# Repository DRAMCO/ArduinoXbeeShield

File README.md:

# Arduino Xbee Shield by [DRAMCO](www.dramco.be)

## Required Hardware

- Xbee module
- [Digi XBee interface board](https://www.digi.com/products/models/xbib-u-dev)
- Arduino Uno
- DRAMCO XBee Shield

## Getting Started Guide

1. Install [XCTU](https://www.digi.com/products/xbee-rf-solutions/xctu-software/xctu).
2. Connect the XBee module to the [Digi interface board](https://www.digi.com/products/models/xbib-u-dev)
3. Open XCTU and connect to the interface board
4. Configure the XBee module as required. For instance, set the `AP` parameter to API enabled with PPP.
5. Connect the XBee module to the shield
6. Connectthe shield to an Arduino UNO
7. Open your favourite Arduino IDE and download an XBee library. For example [this one](https://github.com/andrewrapp/xbee-arduino).
8. Start designing cool stuff!

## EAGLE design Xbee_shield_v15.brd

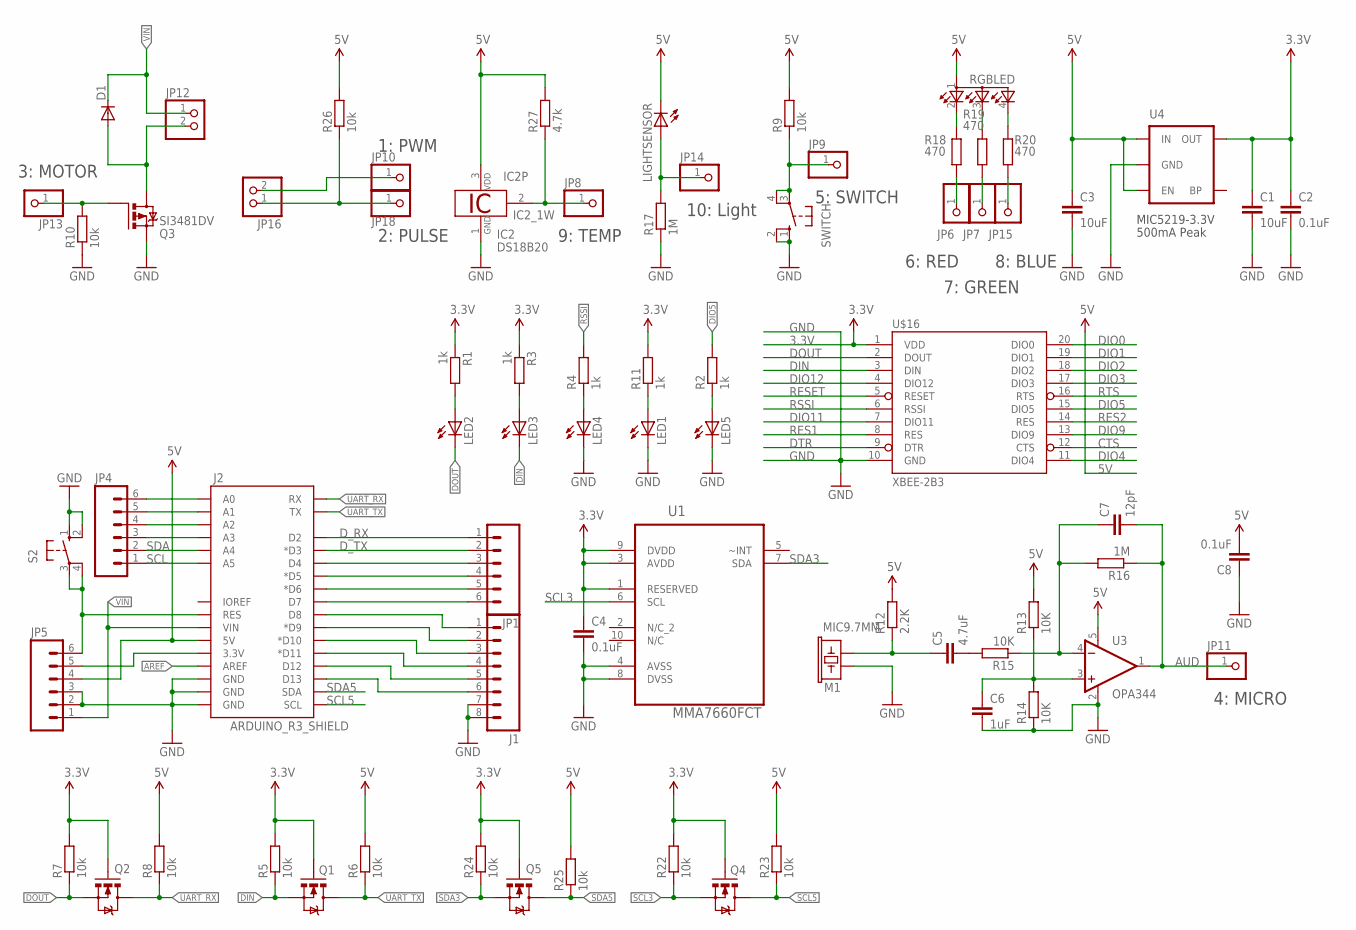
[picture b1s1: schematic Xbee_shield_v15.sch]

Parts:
C1, C3: 10uF; C0805
C2, C4, C8: 0.1uF; C0805
C5: 4.7uF; C0805
C6: 1uF; C0805
C7: 12pF; C0805
D1: DIODE-DO214AA; DO214AA
IC2: DS18B20; TO92-
J1: M08; 1X08_ROUND
J2: ARDUINO_R3_SHIELD; UNO_R3_SHIELD
JP1, JP4, JP5: M06SIP; 1X06
JP6, JP7, JP8, JP9, JP10, JP11, JP13, JP14, JP15, JP18: PINHD-1X1; 1X01
JP12, JP16: PINHD-1X2; 1X02
LED1, LED2, LED3, LED4, LED5: LEDCHIPLED_0805; CHIPLED_0805
LIGHTSENSOR: LED5MM
M1: MIC9.7MM; MIC-9.7MM
Q1, Q2, Q4, Q5: MOSFET-NCHANNELSMD; SOT23-3
Q3: SI3481DV; TSOP-6.PAC
R1, R2, R3, R4, R11: 1k; R0805
R5, R6, R7, R8, R9, R10, R22, R23, R24, R25, R26: 10k; R0805
R12: 2.2K; R0805
R13, R14, R15: 10K; R0805
R16, R17: 1M; R0805
R18, R19, R20: 470; R0805
R27: 4.7k; R0805
RGBLED: TOPLED-3; P-LCC-4-3
S2: 10-XX; B3F-10XX
SWITCH: 10-XX; B3F-10XX
U1: MMA7660FCT; DFN300X300X100-10N
U3: OPA344; SOT23-5
U4: V_REG_LDOSMD; SOT23-5
U$16: XBEE-2B3; XBEE-SMD

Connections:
3.3V: C1.1, C2.1, C4.1, Q1.1 (G), Q2.1 (G), Q4.1 (G), Q5.1 (G), R1.1, R3.1, R5.2, R7.2, R11.2, R22.2, R24.2, U1.1 (RESERVED), U1.3 (AVDD), U1.9 (DVDD), U4.5 (OUT), U$16.1 (VDD)
5V: C3.1, C8.2, IC2.3 (VDD), J2.5V, JP5.4, LIGHTSENSOR.K (C), R6.2, R8.2, R9.2, R12.2, R13.2, R23.2, R25.2, R26.2, R27.2, RGBLED.1 (A2), U3.5 (V+), U4.1 (IN), U4.3 (EN)
AREF: J2.AREF
AUD: C7.2, JP11.1, R16.1, U3.1 (OUT)
CTS: U$16.12 (CTS)
DIN: LED3.C, Q1.2 (S), R5.1, U$16.3 (DIN)
DIO0: U$16.20 (DIO0)
DIO1: U$16.19 (DIO1)
DIO2: U$16.18 (DIO2)
DIO3: U$16.17 (DIO3)
DIO4: U$16.11 (DIO4)
DIO5: R2.2, U$16.15 (DIO5)
DIO9: U$16.13 (DIO9)
DIO11: U$16.7 (DIO11)
DIO12: U$16.4 (DIO12)
DOUT: LED2.C, Q2.2 (S), R7.1, U$16.2 (DOUT)
DTR: U$16.9 (DTR)
D_RX: J2.D2, JP1.1
D_TX: J2.D3 (*D3), JP1.2
GND: C1.2, C2.2, C3.2, C4.2, C6.2, C8.1, IC2.1 (GND), J1.7, J1.8, J2.GND@0 (GND), J2.GND@1 (GND), J2.GND@2 (GND), JP5.2, JP5.3, LED1.C, LED4.C, LED5.C, M1.2, Q3.4 (S), R10.1, R14.1, R17.1, S2.1 (S), S2.2 (S1), SWITCH.1 (S), SWITCH.2 (S1), U1.4 (AVSS), U1.8 (DVSS), U3.2 (V-), U4.2 (GND), U$16.10 (GND)
unnamed: LED2.A, R1.2
unnamed: LED4.A, R4.1
unnamed: J1.6, J2.D13
unnamed: LED3.A, R3.2
unnamed: J2.A0, JP4.6
unnamed: J2.A1, JP4.5
unnamed: J2.A2, JP4.4
unnamed: J2.RES, JP5.6, S2.3, S2.4 (P1)
unnamed: JP9.1, R9.1, SWITCH.3, SWITCH.4 (P1)
unnamed: IC2.2 (1W), JP8.1, R27.1
unnamed: JP10.1, JP16.2
unnamed: C5.1, M1.1, R12.1
unnamed: C7.1, R15.1, R16.2, U3.4 (-IN)
unnamed: C5.2, R15.2
unnamed: C6.1, R13.1, R14.2, U3.3 (+IN)
unnamed: J1.1, J2.D8
unnamed: J1.2, J2.D9 (*D9)
unnamed: JP13.1, Q3.3 (G), R10.2
unnamed: D1.A, JP12.2, Q3.1 (D), Q3.2 (D), Q3.5 (D), Q3.6 (D)
unnamed: JP14.1, LIGHTSENSOR.A, R17.2
unnamed: J2.A3, JP4.3
unnamed: JP16.1, JP18.1, R26.1
unnamed: J2.3.3V, JP5.5
unnamed: R18.2, RGBLED.2 (CRED)
unnamed: R19.2, RGBLED.3 (CBLUE)
unnamed: R20.2, RGBLED.4 (CGREEN)
unnamed: JP6.1, R18.1
unnamed: J1.3, J2.D10 (*D10)
unnamed: JP7.1, R19.1
unnamed: JP15.1, R20.1
unnamed: LED1.A, R11.1
unnamed: J1.4, J2.D11 (*D11)
unnamed: J1.5, J2.D12
unnamed: LED5.A, R2.1
unnamed: J2.D4, JP1.3
unnamed: J2.D5 (*D5), JP1.4
unnamed: J2.D6 (*D6), JP1.5
unnamed: J2.D7, JP1.6
RES1: U$16.8 (RES)
RES2: U$16.14 (RES)
RESET: U$16.5 (RESET)
RSSI: R4.2, U$16.6 (RSSI)
RTS: U$16.16 (RTS)
SCL: J2.A5, JP4.1
SCL3: Q4.2 (S), R22.1, U1.6 (SCL)
SCL5: J2.SCL, Q4.3 (D), R23.1
SDA: J2.A4, JP4.2
SDA3: Q5.2 (S), R24.1, U1.7 (SDA)
SDA5: J2.SDA, Q5.3 (D), R25.1
UART_RX: J2.RX, Q2.3 (D), R8.1
UART_TX: J2.TX, Q1.3 (D), R6.1
VIN: D1.C, J2.VIN, JP5.1, JP12.1

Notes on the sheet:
500mA Peak
MIC5219-3.3V
1: PWM
2: PULSE
3: MOTOR
10: Light
5: SWITCH
6: RED
7: GREEN
8: BLUE
9: TEMP
4: MICRO

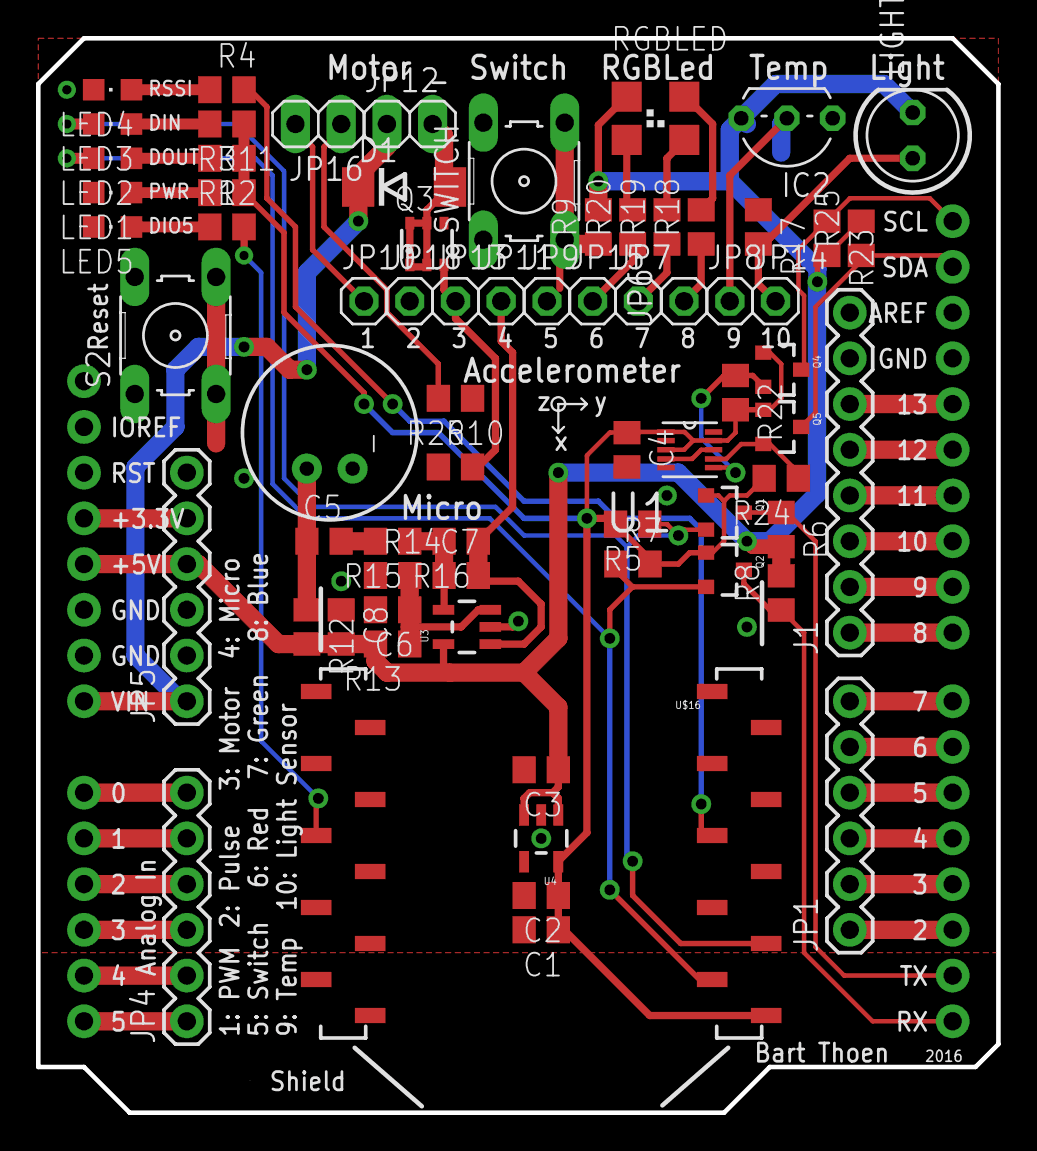
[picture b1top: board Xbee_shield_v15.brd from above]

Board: 2 copper layers, 53.3 x 59.7 mm, 72 parts (1 on the bottom side), 57 nets.

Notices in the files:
parts and their libraries:
SparkFun-DiscreteSemi: Licensing: CC v3.0 Share-Alike You are welcome to use this library for commercial purposes.
SparkFun-Boards: Licensing: Creative Commons ShareAlike 4.0 International - https://creativecommons.org/licenses/by-sa/4.0
